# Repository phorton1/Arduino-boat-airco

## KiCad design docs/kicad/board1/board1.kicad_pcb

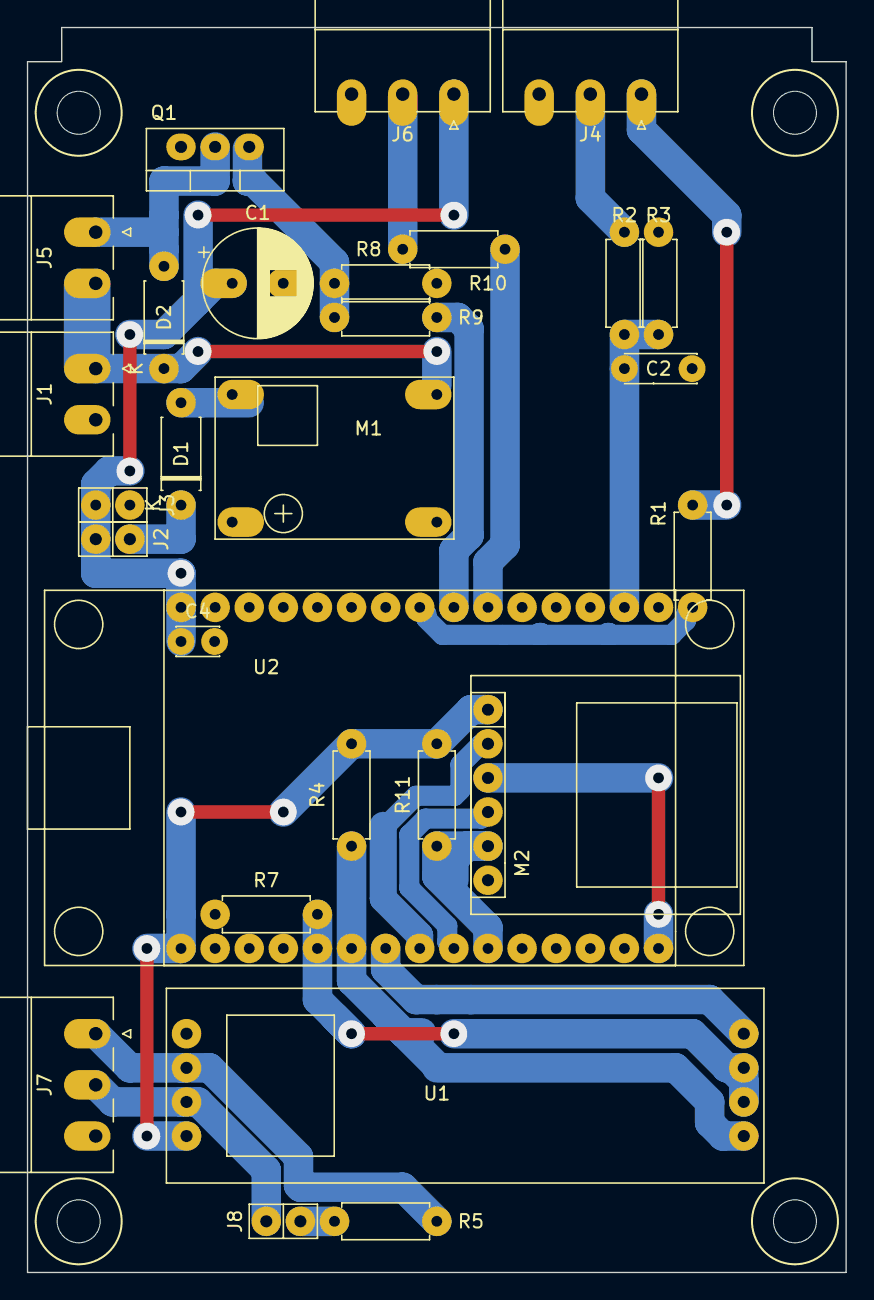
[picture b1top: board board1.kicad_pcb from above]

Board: 2 copper layers, 61.0 x 92.7 mm, 28 parts (0 on the bottom side), 25 nets.

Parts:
C1: 100uf; CP_my100uf
C2: 2.2uf; myCapTantulum2
C4: 0.1uf; myCapCeramicSmall
D1: 1N4003; myDiodeSchotsky
D2: 1N5818; myDiodeSchotsky
J1: 12 IN; myPheonix2x3.81_right
J2: 5V Jump; myPinHeader_1x02
J3: 5V Test; myPinSocket_1x02
J4: SENSOR; myPheonix3x3.81_right
J5: PUMP; myPheonix2x3.81_right
J6: WS2812_B; myPheonix3x3.81_right
J7: RS485; myPheonix3x3.81_right
J8: RS485_TERMINATOR; myPinHeader_1x02
M1: BUCK01; buck-mini360
M2: SD_TYP0; SDCardReader_flipped
Q1: IRLZ44N; TO-220-3_Vertical
R1, R2: 1K; myResistor
R3: 100K; myResistor
R4, R7, R10, R11: 10K; myResistor
R5: 120; myResistor
R8, R9: 220; myResistor
U1: RS485_MODULE; RS485_Module
U2: ESP32_DEV_0; myESP32DEV0

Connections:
+3V3: M2.6, R4.2, R11.2, U1.8, U2.30
+5V: C1.1, C4.1, J2.2, J3.2, J6.1, U2.1
DRIVE_ROD: J4.1, R1.1
GND: C1.2, C2.2, C4.2, J1.2, J3.1, J4.3, J6.3, J7.3, M1.1, M1.2, M2.1, Q1.3, R3.2, R7.2, R10.2, U1.5, U2.2, U2.29
MISO: M2.2, R11.1, U2.21
MOSI: M2.4, U2.16
unnamed: D1.1, J2.1
unnamed: D1.2, M1.3
unnamed: J6.2, R8.2
unnamed: J8.2, R5.1
unnamed: Q1.1, R9.2, R10.1
PUMP: R9.1, U2.9
PUMP+: D2.1, J1.1, J5.2, M1.4
PUMP-: D2.2, J5.1, Q1.2
RS485_A: J7.2, J8.1, U1.7
RS485_B: J7.1, R5.2, U1.6
RX2: R4.1, U1.1, U2.25
SCLK: M2.3, U2.22
SDCS: M2.5, U2.23
SENSOR: C2.1, R2.2, R3.1, U2.14
SENSOR_ROD: J4.2, R2.1
S_DRIVE: R1.2, U2.8
TX2: U1.4, U2.24
TX_EN: R7.1, U1.2, U1.3, U2.26
WS2812B: R8.1, U2.10

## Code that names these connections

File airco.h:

//----------------------------------------------
// Constants for airco.ino
//----------------------------------------------

#pragma once

#include <myIOTDevice.h>

#define WITH_WEBASTO	1
	// set to 0 to make this "just a drain pump controller"
	//allows for use without the RS485/Webasto monitor

#if WITH_WEBASTO
	#define WITH_DBG_RAW_PACKETS	1
		// set to 0 to remove the DBG_RAW_PACKETS command, the one-shot
		// raw RS485 byte capture in aircoTask(), and its printer
#else
	#define WITH_DBG_RAW_PACKETS	0
#endif



//=========================================================
// pins
//=========================================================

#define PIN_ALIVE_LED	2
#define PIN_TX_EN		4
#define PIN_RX2			16
#define PIN_TX2			17
#define PIN_PUMP		33
#define PIN_SENSOR		36
#define PIN_SDRIVE		25
#define PIN_LED			32


// SD CARD
// PIN_MOSI		23
// PIN_MISO		19
// PIN_SCLK		18
// PIN_SDCS		5


//------------------------
// myIOT definition
//------------------------

#define AIRCO_DEVICE			"airco_device"
#define AIRCO_DEVICE_VERSION	"ac2.0"
#define AIRCO_DEVICE_URL		"https://github.com/phorton1/Arduino-boat-airco"

// AIRCO

#if WITH_WEBASTO
	#define ID_AIRCO_STATE			"AIRCO_STATE"		// readonly string containing airco state
	#define ID_AIRCO_ERROR			"AIRCO_ERROR"		// readonly string containing cumulative airco errors
	#define ID_AIRCO_BUS			"AIRCO_BUS"			// readonly "UP|DOWN since=<epoch> outages=<n> last_down=<epoch> down_secs=<n>"
		// the RS485 bytes flowing (UP) or not (DOWN, i.e. the airco has lost power);
		// changes ONLY on an up/down edge, so it can be polled over http
	#define ID_TEST_NO_PACKETS		"TEST_NO_PACKETS"	// switch (not saved); fakes a DOWN in AIRCO_BUS and the log, nothing else
#endif

#if WITH_DBG_RAW_PACKETS
	#define ID_DBG_RAW_PACKETS		"DBG_RAW_PACKETS"	// command; one-shot capture of raw RS485 bytes, printed with LOGU
#endif

// DRAIN PUMP

#define ID_DRAIN_STATE			"DRAIN_STATE"		// readonly string containing drain pump state
#define ID_DRAIN_MODE			"DRAIN_MODE"		// enum select

#define ID_STATE_LAST_RUN		"STATE_LAST_RUN"	// most recent drain pump error/notice, if any
#define ID_TIME_LAST_RUN    	"TIME_LAST_RUN"		// statistics regarding the last completed run
#define ID_DUR_LAST_RUN     	"DUR_LAST_RUN"
#define ID_SINCE_LAST_RUN   	"SINCE_LAST_RUN"

#define ID_ON_THRESH			"ON_THRESH"			// int; default=500;   min=1; max=4094;
#define ID_OFF_THRESH			"OFF_THRESH"		// int; default=10;	   min=1; max=4094;
#define ID_EXTRA_TIME			"EXTRA_TIME"		// int seconds; default=0; min=0; max=30;
#define ID_MAX_TIME				"MAX_TIME"			// int seconds; default=150;  min=0 (off); max=360	 (6 minutes)
#define ID_COOLDOWN_TIME		"COOLDOWN_TIME"		// int seconds; default=60 min=10; max=900 (15 minutes)
#define ID_IDLE_TIME			"IDLE_TIME"			// int seconds; default=3600; min=0 (off); max=84600 (1 day)
#define ID_IDLE_THRESH			"IDLE_THRESH"		// int; default=60;    min=1; max=4094;

#define ID_DRIVE_TIME_US		"DRIVE_TIME_US"		// int microseconds; default=1000; min=100; max=3000;
	// time in microseconds between turning the DRIVE on and reading the SENSOR.
	// The default is 1000 us where higher settings lead directly to higher readings.
#define ID_SAMPLE_TIME			"SAMPLE_TIME_MS"	// in ms, default=1000, min=100, max=3000
	// how often, in ms, to take a sample and add it to the circular buffer
	// This is also the maximum granularity of the pump being turned on and off
#define ID_NUM_SAMPLES			"NUM_SAMPLES"		// int; default=5; min=1; max=20
	// Number of samples in circular buffer
	// THIS SETS A "SLOP" EXTRA PUMP RUN-DRY TIME !!!

#define ID_LOG_WINDOW			"LOG_WINDOW"		// int; default=50; min=0 (off); max=100;
	// Sets a window for how far the sensor_avg must move before a log entry is created.
	// Note that pump on, extra, cooldown, and pump off already generate log entries,
	// so this is mostly used to guage the rise time, and is set to avoid slosh effects.

// USER INTERFACE

#define ID_CLEAR_ERROR			"CLEAR_ERROR"
#define ID_UI_INTERVAL			"UI_INTERVAL"		// int milliseconds; default=1000; min=1000; max=30000 (5 minutes)
#define ID_LED_BRIGHTNESS		"LED_BRIGHTNESS"

#define ID_DRAIN_HISTORY     	"DRAIN_HISTORY"
#define ID_CHART				"CHART"


// enums

#define MAX_SENSOR_SAMPLES		20

#define DRAIN_MODE_OFF			0
#define DRAIN_MODE_ON			1
#define DRAIN_MODE_FORCE		2

#define DRAIN_FLAG_FORCE		0x0001
#define DRAIN_FLAG_IDLE_RUN		0x0002
#define DRAIN_FLAG_INITIAL_RUN	0x0004
#define DRAIN_FLAG_TOO_LONG		0x0010



class aircoDevice : public myIOTDevice
{
public:

    aircoDevice() {}
    ~aircoDevice() {}

	virtual bool hasPlot() override    { return true; }

#if WITH_WEBASTO
	static String 	_airco_state_string;		// built string
	static String 	_airco_error_string;		// built string
	static String 	_airco_bus_string;			// built string; see ID_AIRCO_BUS
	static bool		_test_no_packets;			// see ID_TEST_NO_PACKETS
#endif

	static String 	_drain_state_string;		// built string
	static uint32_t	_drain_mode;				// enum

	static String 	_state_last_run;			// built string
    static time_t   _time_last_run;
    static int      _since_last_run;
    static int      _dur_last_run;

	static int		_on_thresh;			// vs average of analog reads
	static int		_off_thresh;		// vs average of analog reads
	static int		_extra_time;		// seconds
	static int		_max_time;			// seconds
	static int		_cooldown_time;		// seconds

	static int		_idle_time;			// seconds
	static int		_idle_thresh;		// low threhold vs average of analog reads

	static int		_drive_time_us;		// microseconds;
	static int		_sample_time;		// milliseconds;
	static int		_num_samples;

	static int 		_log_window;		// sensor reading
	static int		_ui_interval;		// milliseconds
	static int		_led_brightness;

	static String	_drain_history_link;
	static String	_chart_link;

	static int		m_pump_on;
	static time_t 	m_run_start;
	static uint32_t m_run_flags;
	static int 		m_sensor_avg;
	static uint32_t m_flags_last_run;

#if WITH_WEBASTO
	static uint8_t	m_pcb_cond_temp;
	static uint8_t	m_pcb_intake_temp;
	static uint8_t	m_pcb_fan;
	static uint8_t	m_pan_mode;
	static bool		m_have_pcb;		// a PCB packet has been received since boot
#endif

	// implementation
	// in airco.ino

	void handlePixels();
	static void onBrightnessChanged(const myIOTValue *desc, uint32_t val);

	// in aircoData.cpp

#if WITH_WEBASTO
	void initAircoMonitor();
	void handleAircoData();
	void publishBusEvents();
	void updateAircoUI();
	void reportAircoError(const char *msg);
#endif
#if WITH_DBG_RAW_PACKETS
	static void dbgRawPackets();
#endif
	static void clearAircoError();

	// in aircoDrain.cpp

	void handleDrainPump();
	void updateDrainPumpUI();
	void pumpOn(bool on);
	void startCooldown();
	int readDrainSensor(int pin, int *avg);

	static void onDrainModeChanged(const myIOTValue *value, uint32_t val);

	// in aircoHistory.cpp

	void endDrainRun();
	void addLogRecord();
	String onCustomLink(const String &path,  const char **mime_type) override;
};



extern aircoDevice *airco;

extern bool force_pixels;
	// public to mitigate LEDs going off (?!?!) on pump/compressor power surges(?!?!)

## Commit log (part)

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2025-12-15 initial commit after breadboard and considerable testing
2025-12-15 added data submodule
2025-12-15 checked in strange gitMUI extra commit of /src/Arduino/boat/airco/data submodule commit
2025-12-17 myIOT cleanup - got rid of Widget implementations; WITH_MEM_HISTORY and WITH_PLOT defines; re-ordered airco columns
2025-12-18 Added SDCard to /src/boat/airco myIOTDevice; simplified aircoHistory.cpp
2025-12-18 submodule(data) auto_commit(1adaeb45) reworked iotChart.js incremental update scheme starting with Arduino-boat-drainPump
2025-12-18 starting in Arduino-boat-arirco, major rework of iotChart.js and how charts are implemented - use common chart.html instead of specific/extra_data/device_chart.html - eliminates need for extra_data/d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
2025-12-18 comments only
2025-12-18 submodule(data) auto_commit(1efc7b72) rework iotChart.js::determineNumberTicks() starting with drain_pump
2025-12-18 submodule(data) auto_commit(78894e93) change onChartResize() to use create_chart() instead of built in jqplot.replot()
2025-12-18 submodule(data) auto_commit(40916b0c) separate iotChart.js doChart() as init only method from onXXX() UI methods - yet another rework of iotChart.js and myIOTDataLog starting with fridgeController
2025-12-18 submodule(data) auto_commit(b923e44d) back to static html for chart.html; got rid of myIOTDataLog::getChartHtml() starting with tempController
2025-12-18 bring up to latest data/iotChart.js and data/chart.html
2025-12-18 submodule(data) auto_commit(a4e2ed81) change chart.html and iotChart.js to use and remove style "degree_hidden" for devices that chart things with degrees
2025-12-18 submodule(data) auto_commit(a9754dbc) fixed renamed control _degree_type
2025-12-18 submodule(data) auto_commit(03555741) fix malformed chart.html <select id='_chart_period'> text
2025-12-19 submodule(data) auto_commit(1cb3d61a) add onChartResize() back to chart.html
2025-12-19 submodule(data) auto_commit(253976a9) more changes to iotChart.js starting with tempController so at least refresh works *well* if no zooming involved
2025-12-19 commit parents
2025-12-20 submodule(data) auto_commit(eccd1fcc) iotChart.js - added save/restore of series visibility and refactored code
2025-12-24 minor change to test pull-all; committed from boat laptop
2025-12-25 test commit and push for gitMUI
2025-12-31 minor typo bugfix
2025-12-31 submodule(data) auto_commit(2a8db875) add degree_type to myIOT chart_header for use in initializing iotChart.js
2026-02-22 myIOTHTTP.cpp: added special case to do token replacement for "data_name" in chart.html AND updated myIOT devices with charts to pass data_name in chart_link
2026-02-22 submodule(data) auto_commit(37a6a76c) added framework for chart.html to pass "data_name" to allow multiple charts per device; ALSO store most recent chart period in browser storage
2026-02-27 got rid of old drain_pump extra kicad stuff and created new combined airco PCB and designed box
2026-03-01 first COMBINED Airco and DrainPump implementation (built breadboard)
2026-03-01 updated combined BOARD1 - single sensor, resistor silkscreen
2026-03-01 simplify configuiration and logging params
2026-03-01 checkin board1 before milling
2026-03-02 build airco PCB and print box
2026-03-02 update airco preferences.txt to COM6 for new ESP32 no-holes micro-usb
2026-03-03 Fix (re-implmenent) LOG_WINDOW filtering of drain level; minor fix Compressor mode byte
2026-03-04 minor fix to drain pump LOG_WINDOW algorithm
2026-03-04 added smaller (UINT8, CENTIGRADE8, UINT8x10) iotDataLog LOG_TYPES and updated client ctors
2026-03-04 submodule(data) auto_commit(75bcbcb5) iotChart.js - added smaller (UINT8, CENTIGRADE8, UINT8x10) iotDataLog LOG_TYPES and updated client ctors
2026-03-04 submodule(data) auto_commit(d6f02205) added myIotTempSensor "raw" accessors & used to shrink fridgeController.dataLog file size; got rid of FAKE_COMPRESSOR
2026-03-04 got rid of dubious ability to turn myIOT WIFI off and on
2026-03-04 added some 3dp to airco before removing old drainPump repo
2026-03-05 submodule(data) auto_commit(ecc76888) update myIOT data submodule readme.md to remove forward references to actual implmented device repos
2026-03-07 submodule(data) auto_commit(5dbe3136) Save chart visibility and zorders in locsl storage
2026-03-07 Added notion of "initial run" if !_time_last_run && millis()>_idle_time*1000 & m_sensor_avg>_idle_thresh; made CRC_ERRORS record with LOGE; turned on logfile on actual device
2026-03-28 3dp closet_box_cover; add .gitignore *.gcode; copy old drain_angled/strait from /dat/3d ... THAT FOLDER IS OBSOLETE
2026-04-03 re-ordered LEDs on startup - thre's a bug where one or both go off (black) after running a wile
2026-04-03 "fix" new problem with LEDs going off when airco compressor/waterpum go on/off (?!?!) by updating pixels on any UI state change.
2026-04-04 submodule(data) auto_commit(a0279fca) New iotChart tooltips and dataLog record maintenance feature.
2026-04-04 submodule(data) auto_commit(de0689cf) disable Scan/Delete endpoints and just View data records for devices that have graphs, but no SD card
2026-04-04 New Chart Tooltips and DataLog record maintenance feature in myIOT library and updated to all living devices appropriately
2026-04-06 fix minor bug in airco chart link dataname
2026-06-28 submodule(data) auto_commit(eadab9ea) added myIOTDataLog type LOG_COL_TYPE_INT16_10 to support volts (fridgeController)
